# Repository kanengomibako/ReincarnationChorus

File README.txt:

Reincarnation Chorus

ブログ記事→https://drugscore.blog.fc2.com/blog-entry-270.html

PT2399を使用したデジタルコーラスです。

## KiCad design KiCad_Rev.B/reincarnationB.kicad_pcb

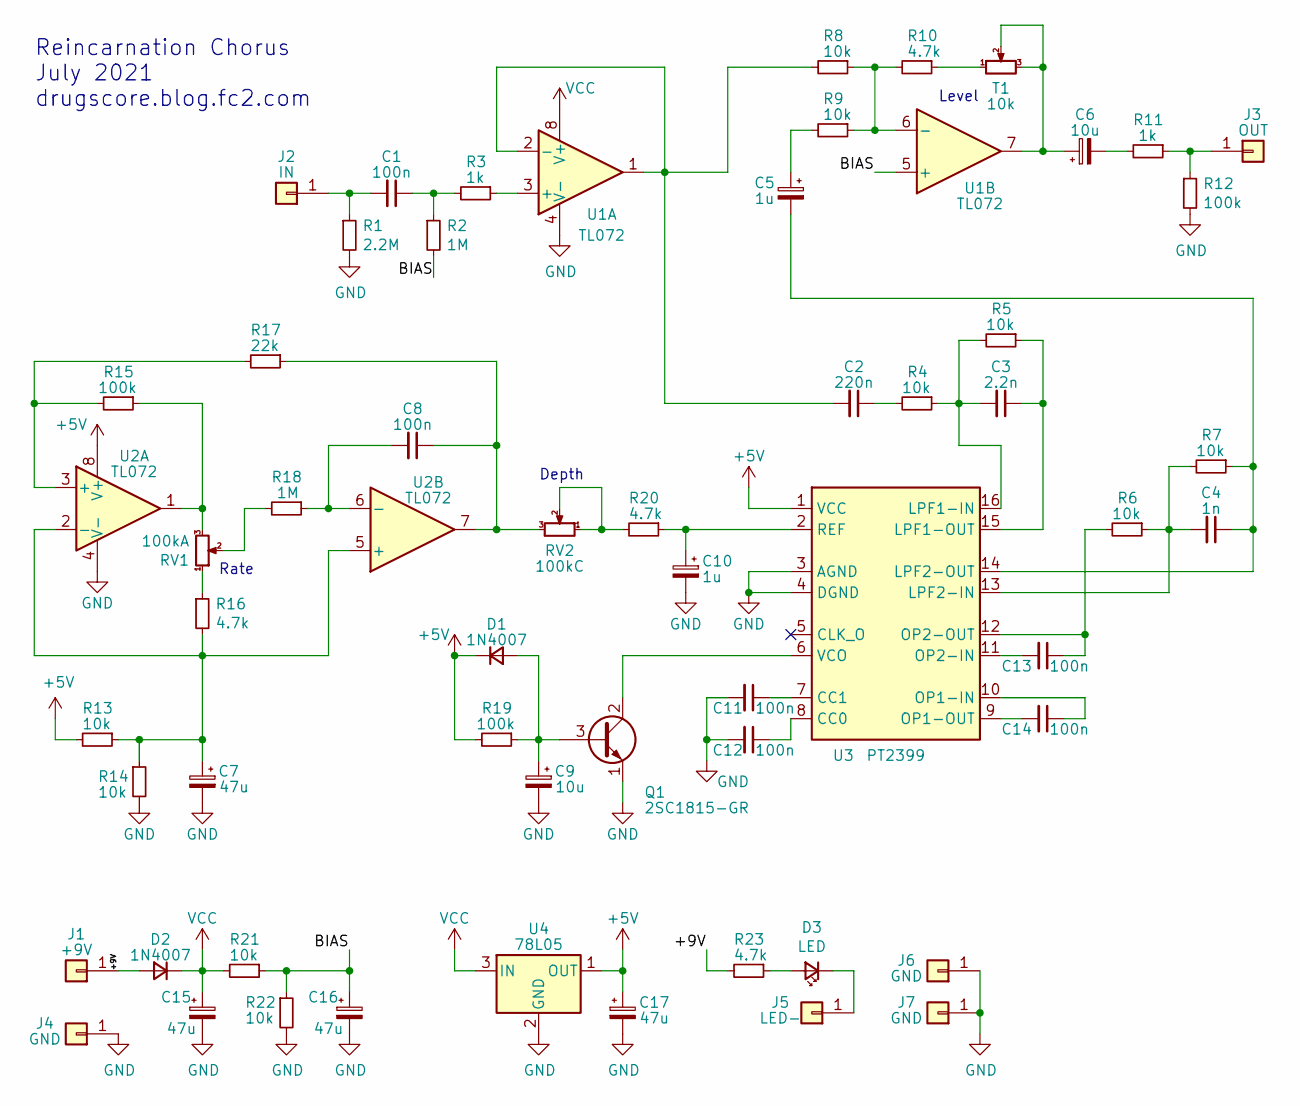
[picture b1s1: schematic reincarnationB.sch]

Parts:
C1, C8, C11, C12, C13, C14: 100n; my_C_Rect1_P5.00mm
C2: 220n; my_C_Rect2_P5.00mm
C3: 2.2n; my_C_Rect1_P5.00mm
C4: 1n; my_C_Rect1_P5.00mm
C5, C10: 1u; my_C_D5.0mm_P2.50mm
C6, C9: 10u; my_C_D5.0mm_P2.50mm
C7, C15, C16, C17: 47u; my_C_D5.0mm_P2.50mm
D1, D2: 1N4007; my_D_P7.62mm
D3: LED; my_LED_3mm
J1: +9V; my_WirePad_0-8mmDrill
J2: IN; my_WirePad_0-8mmDrill
J3: OUT; my_WirePad_0-8mmDrill
J4, J6, J7: GND; my_WirePad_0-8mmDrill
J5: LED-; my_WirePad_0-8mmDrill
Q1: 2SC1815-GR; TO-92_Inline_Wide
R1: 2.2M; my_R_P7.62mm_Horizontal
R2, R18: 1M; my_R_P7.62mm_Horizontal
R3, R11: 1k; my_R_P7.62mm_Horizontal
R4, R5, R6, R7, R8, R9, R13, R14, R21, R22: 10k; my_R_P7.62mm_Horizontal
R10, R16, R20, R23: 4.7k; my_R_P7.62mm_Horizontal
R12, R15, R19: 100k; my_R_P7.62mm_Horizontal
R17: 22k; my_R_P7.62mm_Horizontal
RV1: 100kA; my_pot_5mm
RV2: 100kC; my_pot_5mm
T1: 10k; my_trim
U1, U2: TL072; DIP-8_W7.62mm
U3: PT2399; DIP-16_W7.62mm
U4: 78L05; TO-92_Inline_Wide

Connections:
+5V: C17.1, D1.1 (K), R13.2, R19.2, U2.8 (V+), U3.1 (VCC), U4.1 (OUT)
/+9V: D2.2 (A), J1.1, R23.2
/BIAS: C16.1, R2.2, R21.1, R22.1, U1.5 (+)
GND: C7.2, C9.2, C10.2, C11.2, C12.2, C15.2, C16.2, C17.2, J4.1, J6.1, J7.1, Q1.1 (E), R1.2, R12.2, R14.2, R22.2, U1.4 (V-), U2.4 (V-), U3.3 (AGND), U3.4 (DGND), U4.2 (GND); also elsewhere on the board
unnamed: C1.1, R2.1, R3.2
unnamed: C1.2, J2.1, R1.1
unnamed: C2.1, R4.2
unnamed: C2.2, R8.2, U1.1, U1.2 (-)
unnamed: C3.1, R5.1, U3.15 (LPF1-OUT)
unnamed: C3.2, R4.1, R5.2, U3.16 (LPF1-IN)
unnamed: C4.1, C5.2, R7.1, U3.14 (LPF2-OUT)
unnamed: C4.2, R6.1, R7.2, U3.13 (LPF2-IN)
unnamed: C5.1, R9.2
unnamed: C6.1, T1.2, T1.3, U1.7
unnamed: C6.2, R11.2
unnamed: C7.1, R13.1, R14.1, R16.2, U2.2 (-), U2.5 (+)
unnamed: C8.1, R17.1, RV2.3, U2.7
unnamed: C8.2, R18.1, U2.6 (-)
unnamed: C9.1, D1.2 (A), Q1.3 (B), R19.1
unnamed: C10.1, R20.1, U3.2 (REF)
unnamed: C11.1, U3.7 (CC1)
unnamed: C12.1, U3.8 (CC0)
unnamed: C13.1, R6.2, U3.12 (OP2-OUT)
unnamed: C13.2, U3.11 (OP2-IN)
unnamed: C14.1, U3.10 (OP1-IN)
unnamed: C14.2, U3.9 (OP1-OUT)
unnamed: D3.1 (K), J5.1
unnamed: D3.2 (A), R23.1
unnamed: J3.1, R11.1, R12.1
unnamed: Q1.2 (C), U3.6 (VCO)
unnamed: R3.1, U1.3 (+)
unnamed: R10.1, T1.1
unnamed: R8.1, R9.1, R10.2, U1.6 (-)
unnamed: R15.1, RV1.3, U2.1
unnamed: R15.2, R17.2, U2.3 (+)
unnamed: R16.1, RV1.1
unnamed: R18.2, RV1.2
unnamed: R20.2, RV2.1, RV2.2
VCC: C15.1, D2.1 (K), R21.2, U1.8 (V+), U4.3 (IN)

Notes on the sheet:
Reincarnation Chorus July 2021 drugscore.blog.fc2.com
Depth
Rate
Level

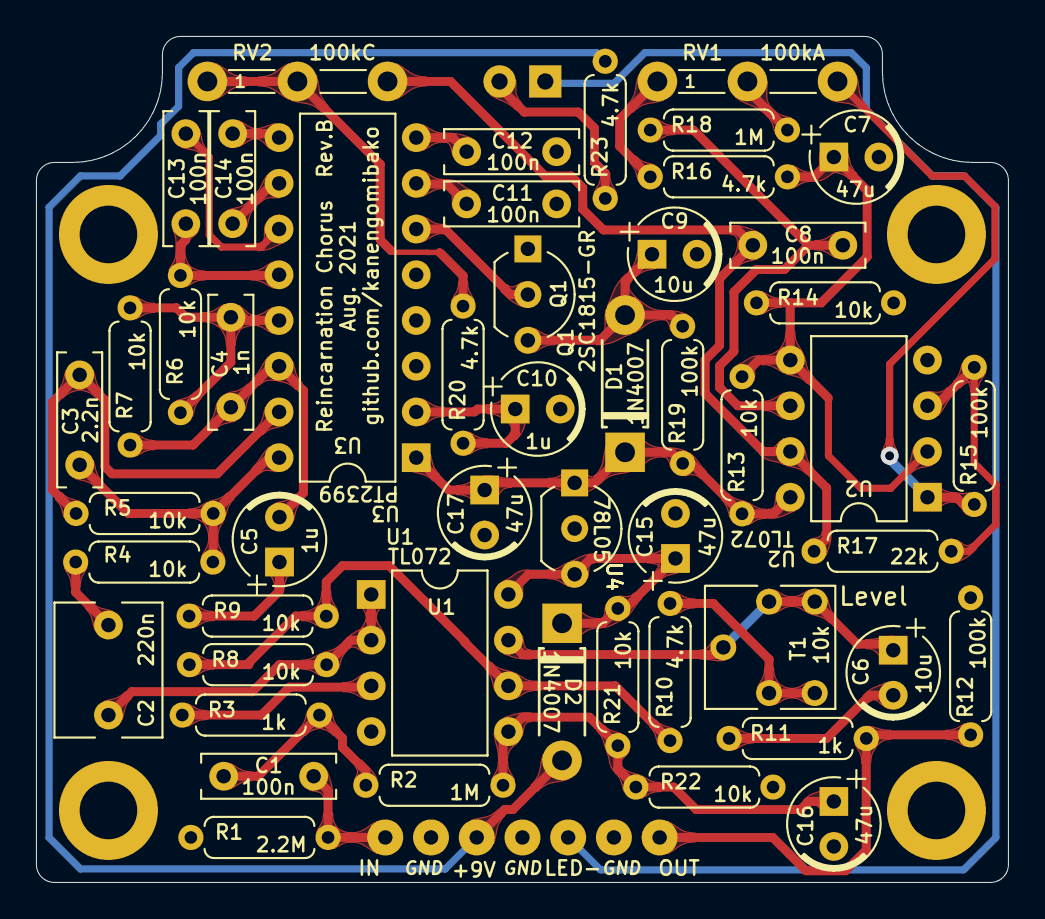
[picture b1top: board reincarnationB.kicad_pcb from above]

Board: 2 copper layers, 54.0 x 47.0 mm, 62 parts (1 on the bottom side), 39 nets.

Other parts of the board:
r: m; MountingHole_3.2mm_M3_ISO14580_Pad
r#2, r#3, r#4: m; MountingHole_3.2mm_M3_ISO14580_Pad

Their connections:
GND: r.1, r#2.1, r#3.1, r#4.1; also elsewhere on the board

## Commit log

2021-09-14 Update KiCad files
    基板画像、Rev.Bデータを追加
